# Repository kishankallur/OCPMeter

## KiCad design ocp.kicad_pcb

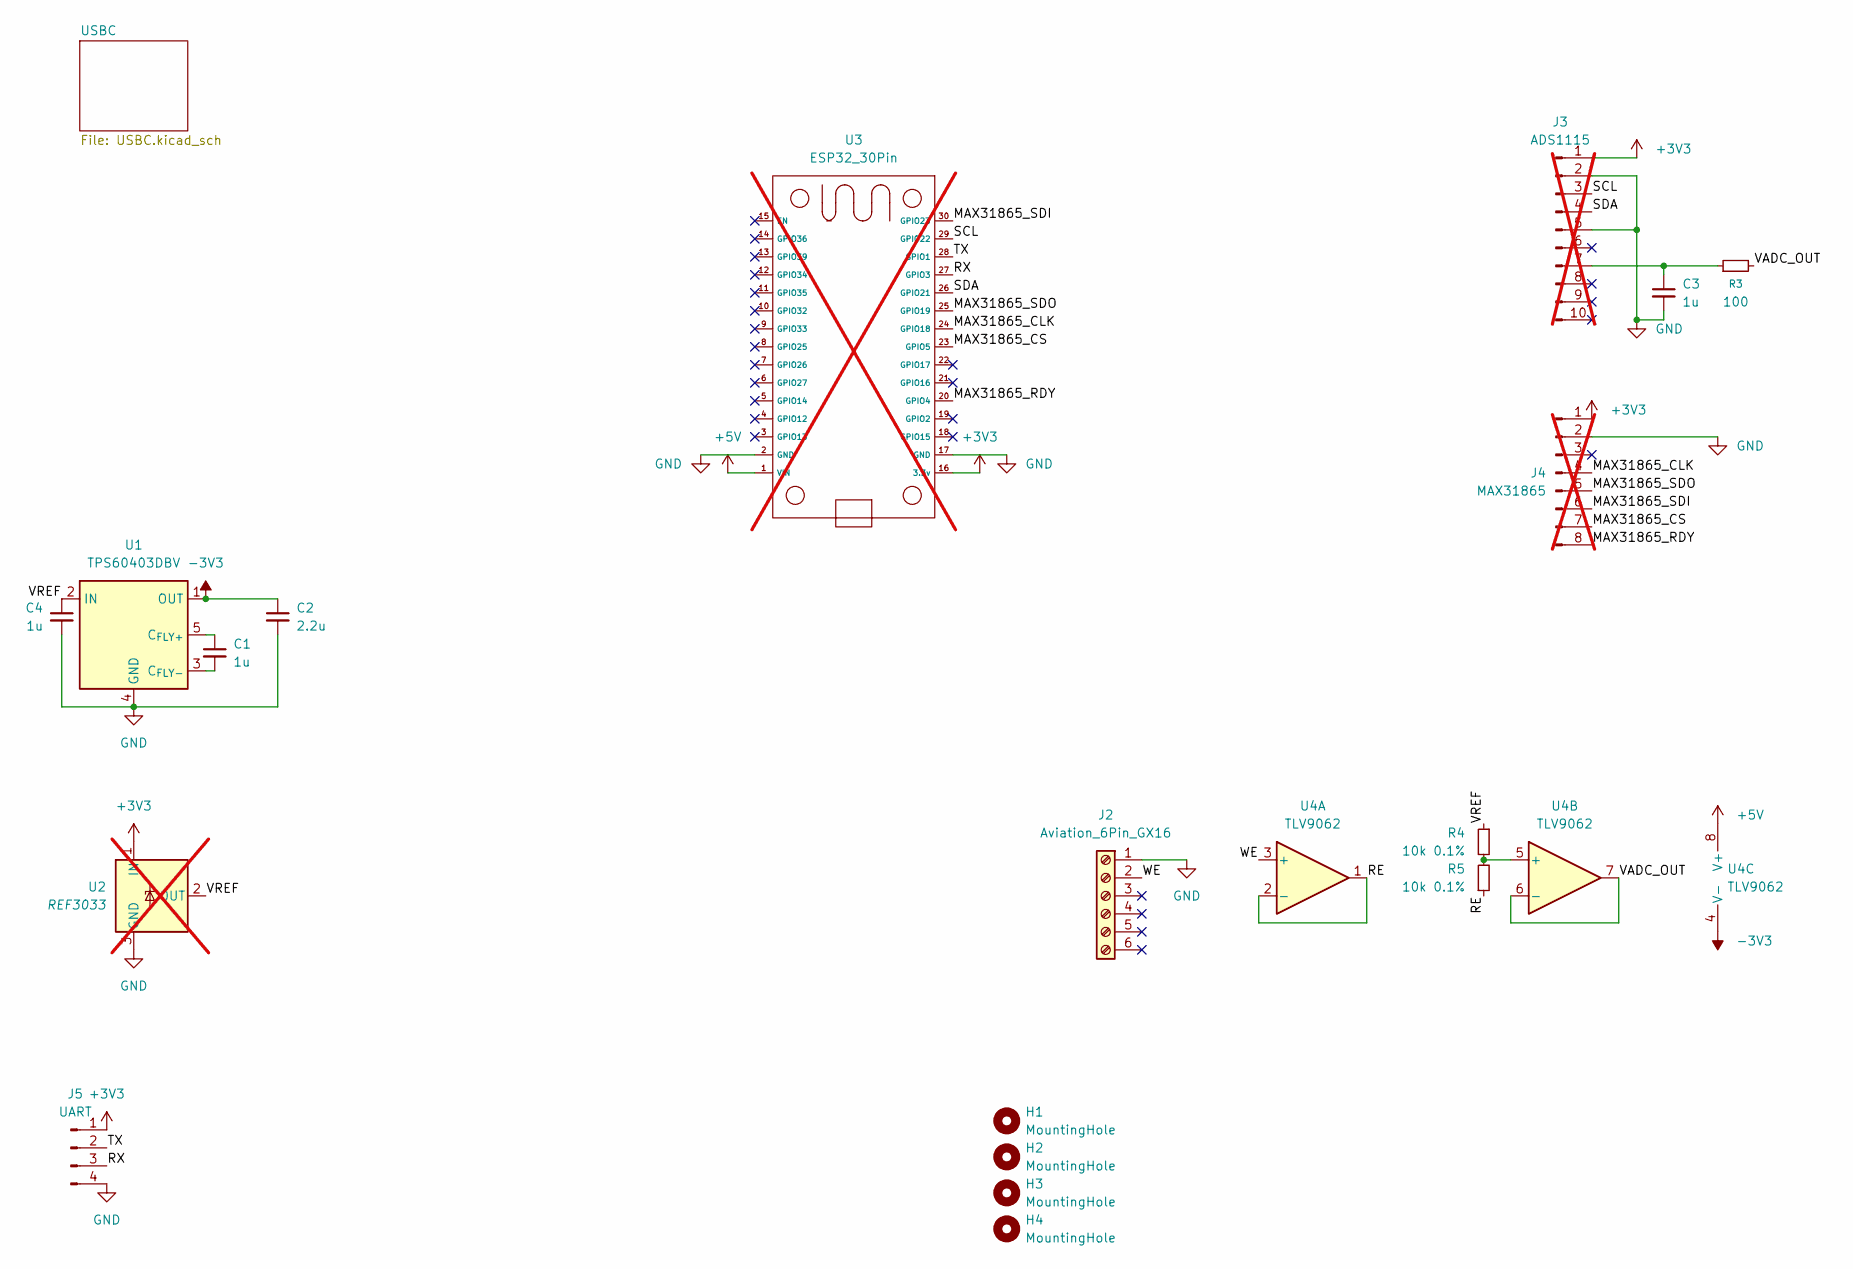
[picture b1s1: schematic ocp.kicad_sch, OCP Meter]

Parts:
C1, C3, C4: 1u; C_0402_1005Metric
C2: 2.2u; C_0603_1608Metric
H1, H2, H3, H4: MountingHole; MountingHole_2.7mm_M2.5
J2: Aviation_6Pin_GX16; TerminalBlock_Phoenix_MKDS-1,5-6-5.08_1x06_P5.08mm_Horizont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
J3: ADS1115; PinHeader_1x10_P2.54mm_Vertical; not fitted
J4: MAX31865; PinHeader_1x08_P2.54mm_Vertical; not fitted
J5: UART; PinHeader_1x04_P2.54mm_Vertical
R3: 100; R_0603_1608Metric
R4, R5: 10k 0.1%; R_0603_1608Metric
U1: TPS60403DBV; SOT-23-5
U2: REF3033; SOT-23; not fitted
U3: ESP32_30Pin; not fitted
U4: TLV9062; TSSOP-8_4.4x3mm_P0.65mm

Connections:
+3V3: J3.1, J4.1, J5.1, U2.1 (IN), U3.16 (3.3v)
+5V: U3.1 (VIN), U4.8 (V+); also elsewhere on the board
-3V3: C2.1, U1.1 (OUT), U4.4 (V-)
/MAX31865_CLK: J4.4, U3.24 (GPIO18)
/MAX31865_CS: J4.7, U3.23 (GPIO5)
/MAX31865_RDY: J4.8, U3.20 (GPIO4)
/MAX31865_SDI: J4.6, U3.30 (GPIO23)
/MAX31865_SDO: J4.5, U3.25 (GPIO19)
/RE: R5.1, U4.1, U4.2 (-)
/RX: J5.3, U3.27 (GPIO3)
/SCL: J3.3, U3.29 (GPIO22)
/SDA: J3.4, U3.26 (GPIO21)
/TX: J5.2, U3.28 (GPIO1)
/VADC_OUT: R3.2, U4.6 (-), U4.7
/VREF: C4.1, R4.1, U1.2 (IN), U2.2 (OUT)
/WE: J2.2, U4.3 (+)
GND: C2.2, C3.2, C4.2, J2.1, J3.2, J3.5, J4.2, J5.4, U1.4 (GND), U2.3 (GND), U3.2 (GND), U3.17 (GND); also elsewhere on the board
unnamed: C3.1, J3.7, R3.1
unnamed: C1.1, U1.5 (C_{FLY+})
unnamed: C1.2, U1.3 (C_{FLY-})
unnamed: R4.2, R5.2, U4.5 (+)

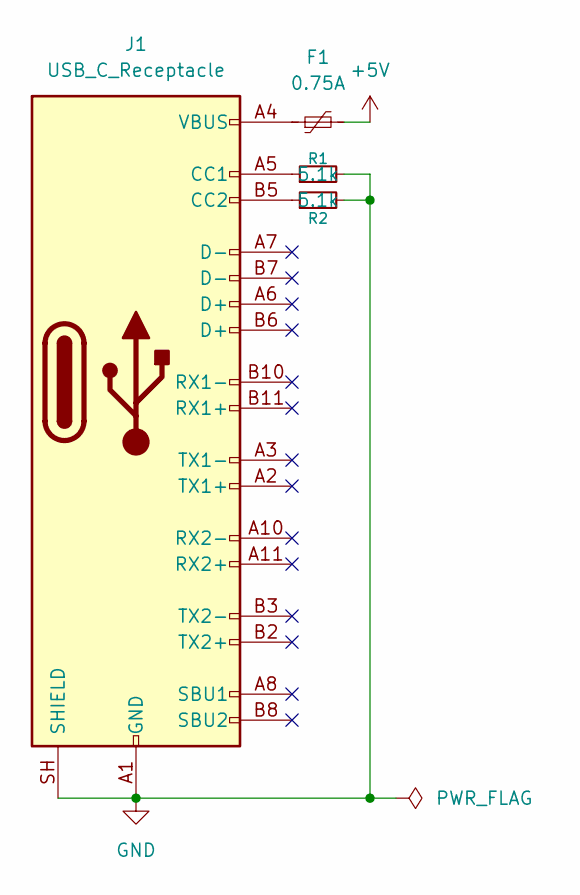
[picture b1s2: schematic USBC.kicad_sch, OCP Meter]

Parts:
F1: 0.75A; Fuse_1206_3216Metric
J1: USB_C_Receptacle; USB_C_Receptacle_G-Switch_GT-USB-7010ASV
R1, R2: 5.1k; R_0402_1005Metric

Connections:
+5V: F1.2; also elsewhere on the board
GND: J1.A1 (GND), J1.A12 (GND), J1.B1 (GND), J1.B12 (GND), J1.SH (SHIELD), R1.2, R2.2; also elsewhere on the board
unnamed: F1.1, J1.A4 (VBUS), J1.A9 (VBUS), J1.B4 (VBUS), J1.B9 (VBUS)
unnamed: J1.A5 (CC1), R1.1
unnamed: J1.B5 (CC2), R2.1

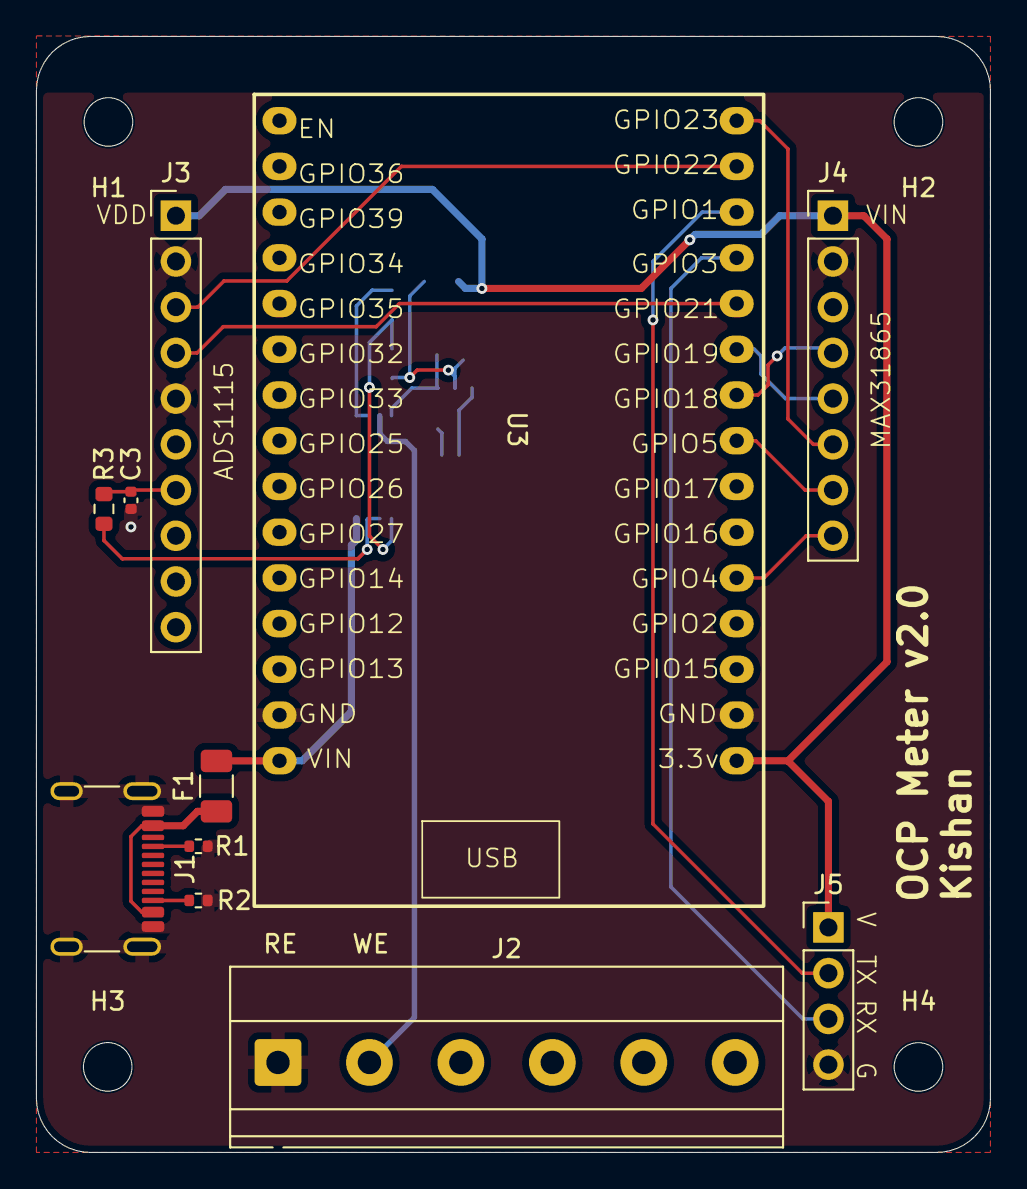
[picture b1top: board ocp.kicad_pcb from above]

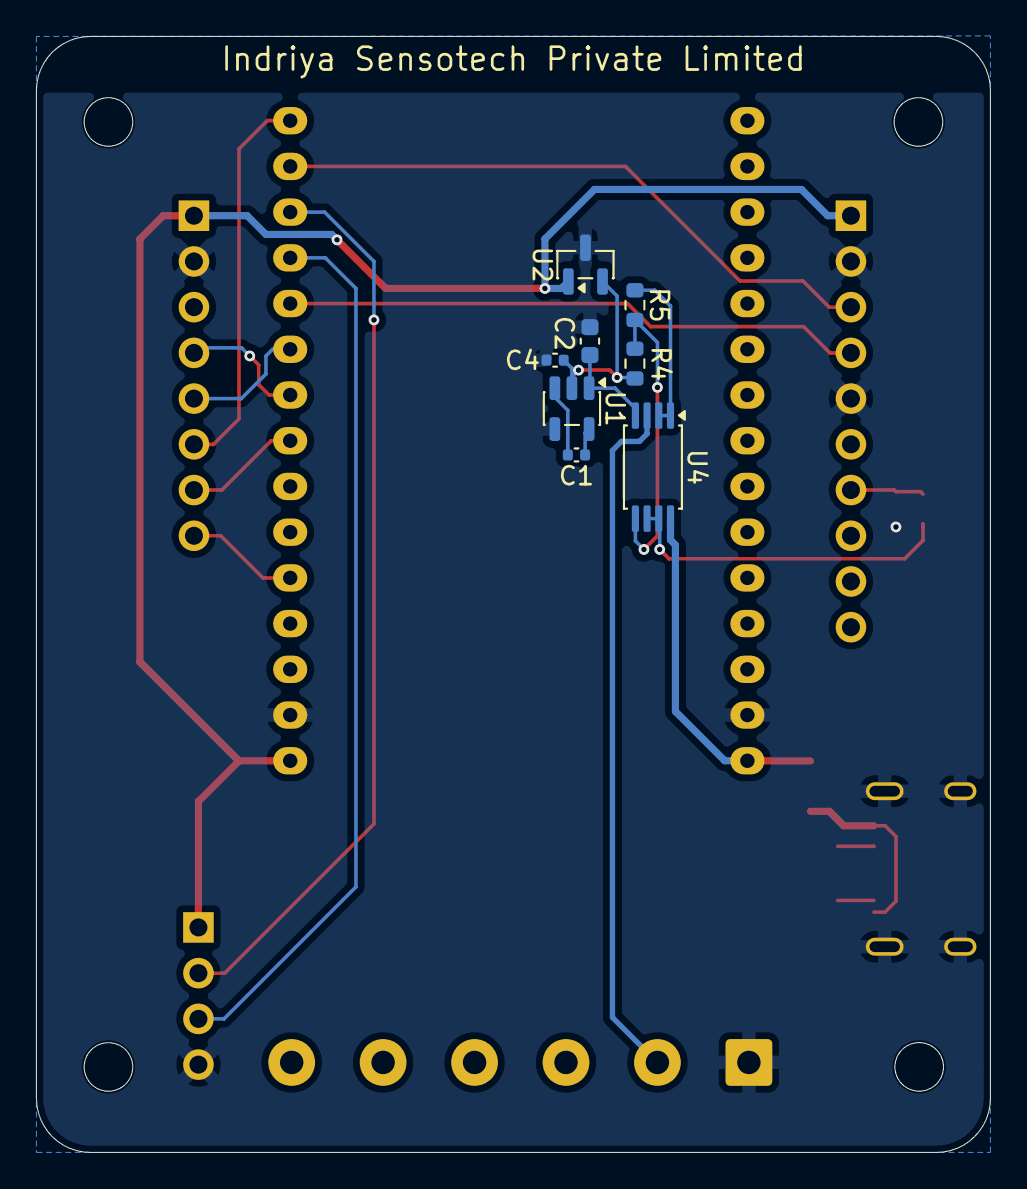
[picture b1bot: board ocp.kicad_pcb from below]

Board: 2 copper layers, 53.0 x 62.0 mm, 23 parts (8 on the bottom side), 24 nets.

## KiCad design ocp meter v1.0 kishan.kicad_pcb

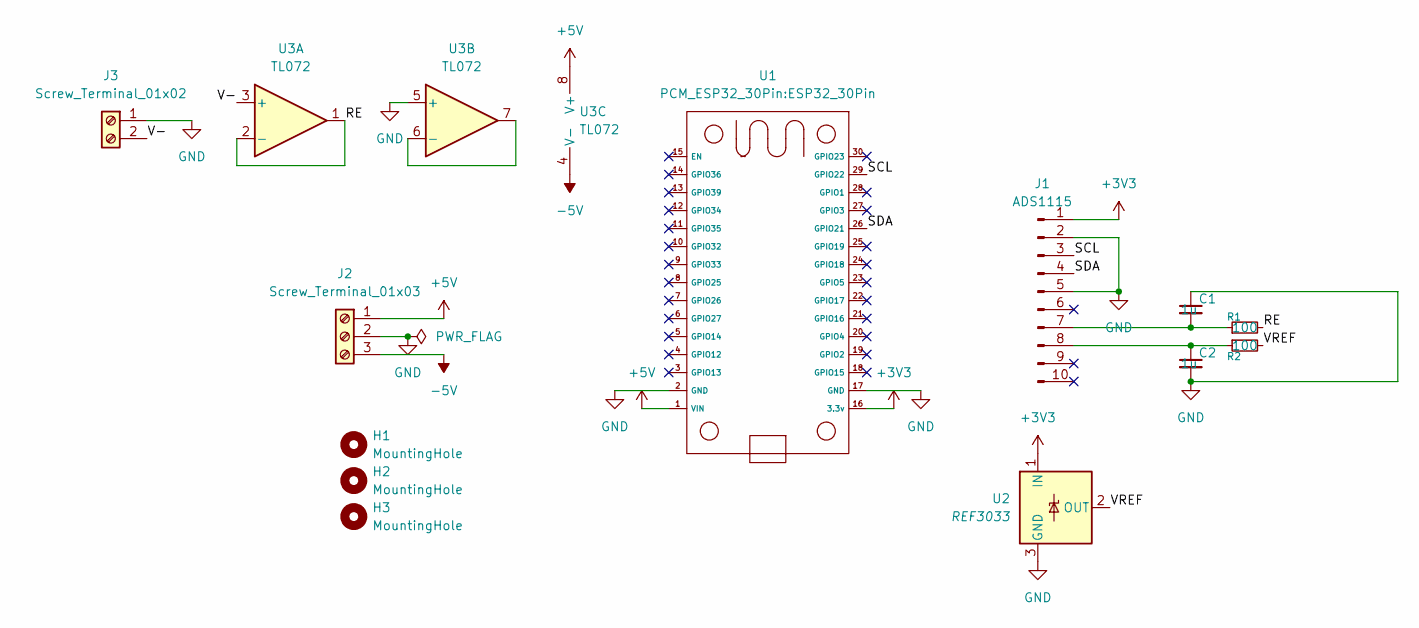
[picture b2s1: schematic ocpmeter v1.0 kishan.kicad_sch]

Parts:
C1, C2: 1u; C_0603_1608Metric
H1, H2, H3: MountingHole; MountingHole_2.7mm_M2.5
J1: ADS1115; PinHeader_1x10_P2.54mm_Vertical
J2: Screw_Terminal_01x03; TerminalBlock_Phoenix_MKDS-1,5-3-5.08_1x03_P5.08mm_Horizont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
J3: Screw_Terminal_01x02; TerminalBlock_Phoenix_MKDS-1,5-2-5.08_1x02_P5.08mm_Horizont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
R1, R2: 100; R_0603_1608Metric
U1: ESP32_30Pin
U2: REF3033; SOT-23
U3: TL072; DIP-8_W7.62mm

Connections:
+3V3: J1.1, U1.16 (3.3v), U2.1 (IN)
+5V: J2.1, U1.1 (VIN), U3.8 (V+)
-5V: J2.3, U3.4 (V-)
/RE: R1.2, U3.1, U3.2 (-)
/SCL: J1.3, U1.29 (GPIO22)
/SDA: J1.4, U1.26 (GPIO21)
/V-: J3.2, U3.3 (+)
/VREF: R2.2, U2.2 (OUT)
GND: C1.1, C2.2, J1.2, J1.5, J2.2, J3.1, U1.2 (GND), U1.17 (GND), U2.3 (GND), U3.5 (+)
unnamed: C1.2, J1.7, R1.1
unnamed: C2.1, J1.8, R2.1
unnamed: U3.6 (-), U3.7

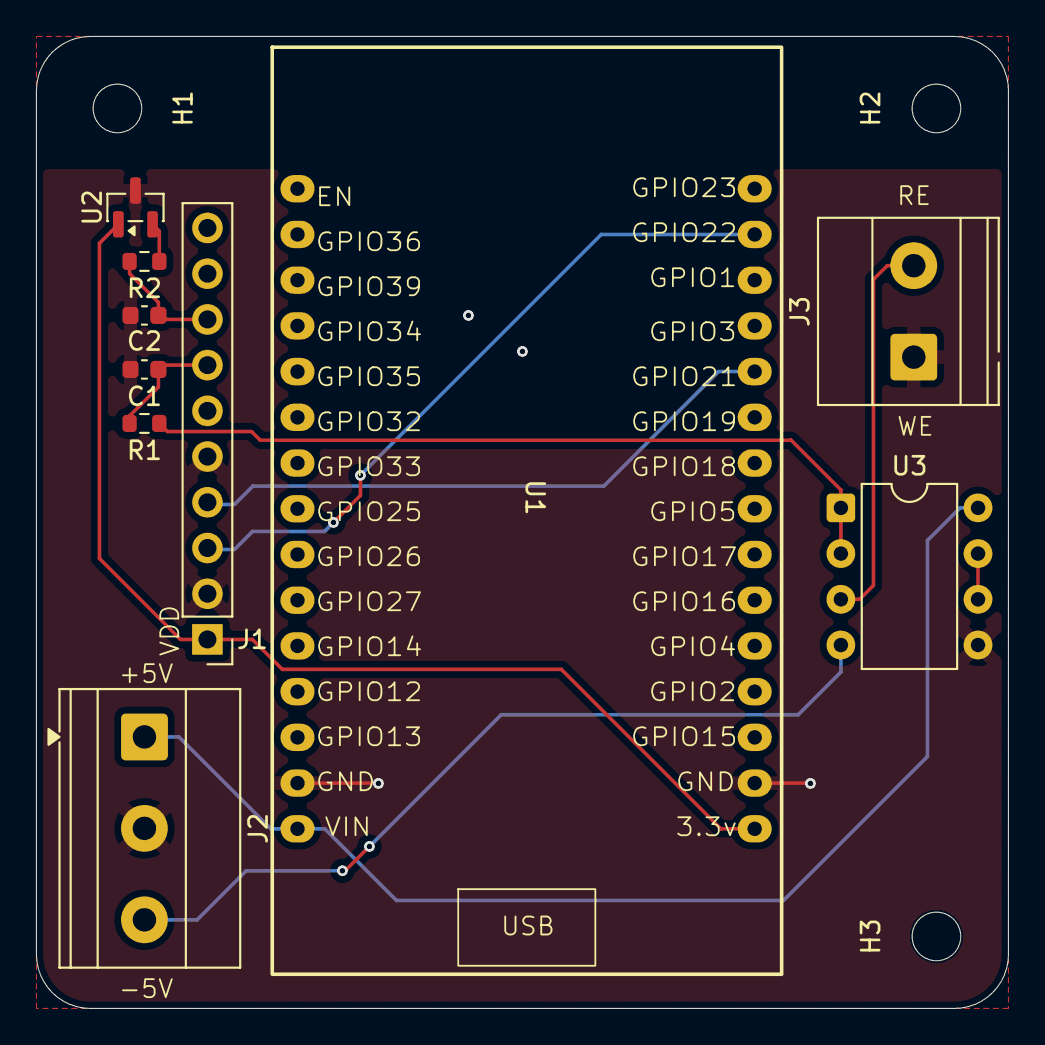
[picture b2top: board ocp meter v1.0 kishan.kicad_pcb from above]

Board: 2 copper layers, 54.0 x 54.0 mm, 13 parts (0 on the bottom side), 12 nets.
